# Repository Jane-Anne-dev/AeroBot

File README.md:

# Starbie

Aerobot is a personal desk buddy. It can be any shape, the goal is to be creative. I t has a motion sensor which allows aerobot  to know if tis being moved around.
shake it and its face moves!
## What it is
It sits on your desk as a companion. You can assign different functions with the buttons and you can play with it if you're bored.

It is inspired by the starbie, here is the repository: https://github.com/SharKingStudios/Starbie/blob/main/README.md?plain=1
it is equiped with a guide which i followed.

The board includes an oled display, microcontroller and motion sensor

The firmware is in the main.cpp file

The aerobot has 21 expressions:
 Mood button cycle (starts in AUTO at boot, never returns to it):
//     Tap  1 Happy         Tap  2 Wink          Tap  3 Love
//     Tap  4 Sleepy        Tap  5 Cry           Tap  6 Distressed
//     Tap  7 Glare         Tap  8 Mad           Tap  9 Glasses
//     Tap 10 Sleep         Tap 11 Blink upper   Tap 12 Tired
//     Tap 13 Night         Tap 14 Upper lids    Tap 15 Lower lids
//     Tap 16 Blank         Tap 17 "HELLO"       Tap 18 "BYE"
//     Tap 19 "What?"       Tap 20 Scuba Cat (sways side to side)
//     Tap 21 = back to Happy ... and so on forever

It also signals water me when it senses dry soil
The 3rd button turns the screen off
The 4th button recaliberates the mpu6050

The aerobot is now comple. Please access the BOM.md for a proper breakdown of the necessary components. The journal for help with any struggles, as i may have struggled with the same thing. 
The KiCad folder has all the schematics, and pcb render. As well as gerber  file which has to be zipped if you  want to order the pcb I made form JLC PCB.
The main.cpp is the program to be installed in the ESP32 C3. it is built for an oled with the sh1106 driver. If you have a different OLED, just change the libraries and it should work.

There's also the backup firmware which is just a copy of main.cpp in case the file gets missing.

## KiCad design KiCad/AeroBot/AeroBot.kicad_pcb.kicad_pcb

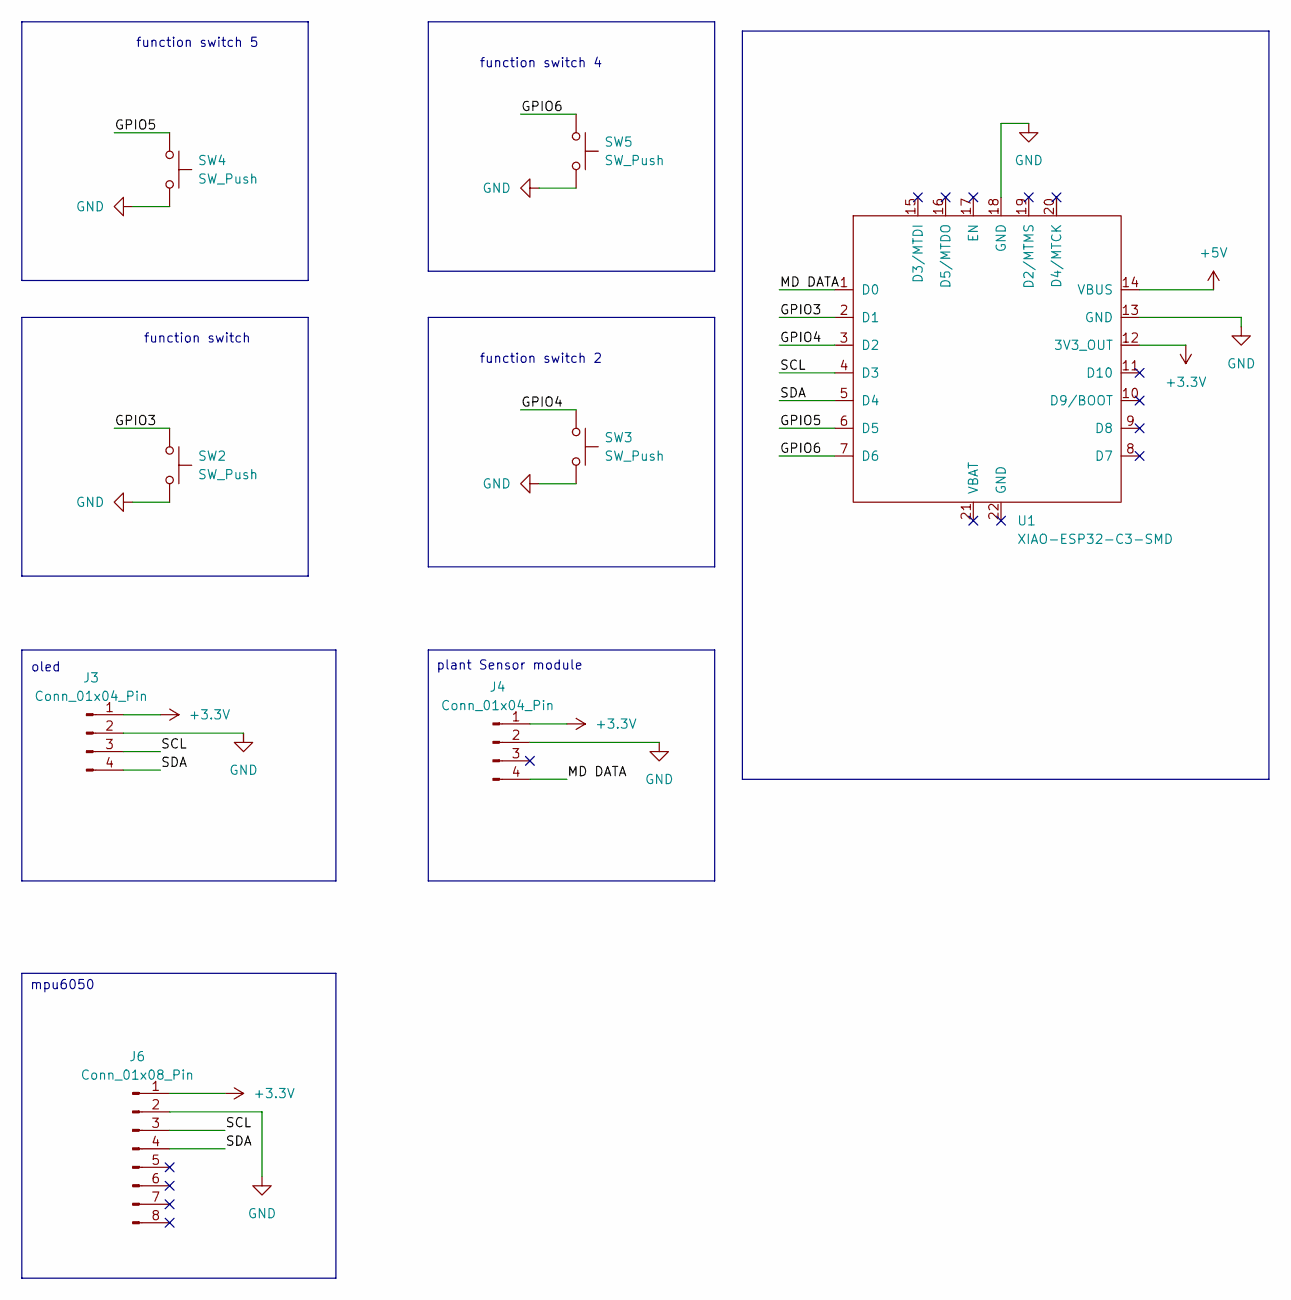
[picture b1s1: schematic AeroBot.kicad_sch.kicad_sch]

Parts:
J3, J4: Conn_01x04_Pin; PinHeader_1x04_P2.54mm_Vertical
J6: Conn_01x08_Pin; PinHeader_1x08_P2.54mm_Vertical
SW2, SW3, SW4, SW5: SW_Push; SW_PUSH_6mm
U1: XIAO-ESP32-C3-SMD

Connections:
+3.3V: J3.1, J4.1, J6.1, U1.12 (3V3_OUT)
+5V: U1.14 (VBUS)
/GPIO3: SW2.1, U1.2 (D1)
/GPIO4: SW3.1, U1.3 (D2)
/GPIO5: SW4.1, U1.6 (D5)
/GPIO6: SW5.1, U1.7 (D6)
/MD DATA: J4.4, U1.1 (D0)
/SCL: J3.3, J6.3, U1.4 (D3)
/SDA: J3.4, J6.4, U1.5 (D4)
GND: J3.2, J4.2, J6.2, SW2.2, SW3.2, SW4.2, SW5.2, U1.13 (GND), U1.18 (GND)

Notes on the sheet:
function switch 5
function switch 4
function switch
plant Sensor module
oled
function switch 2
mpu6050

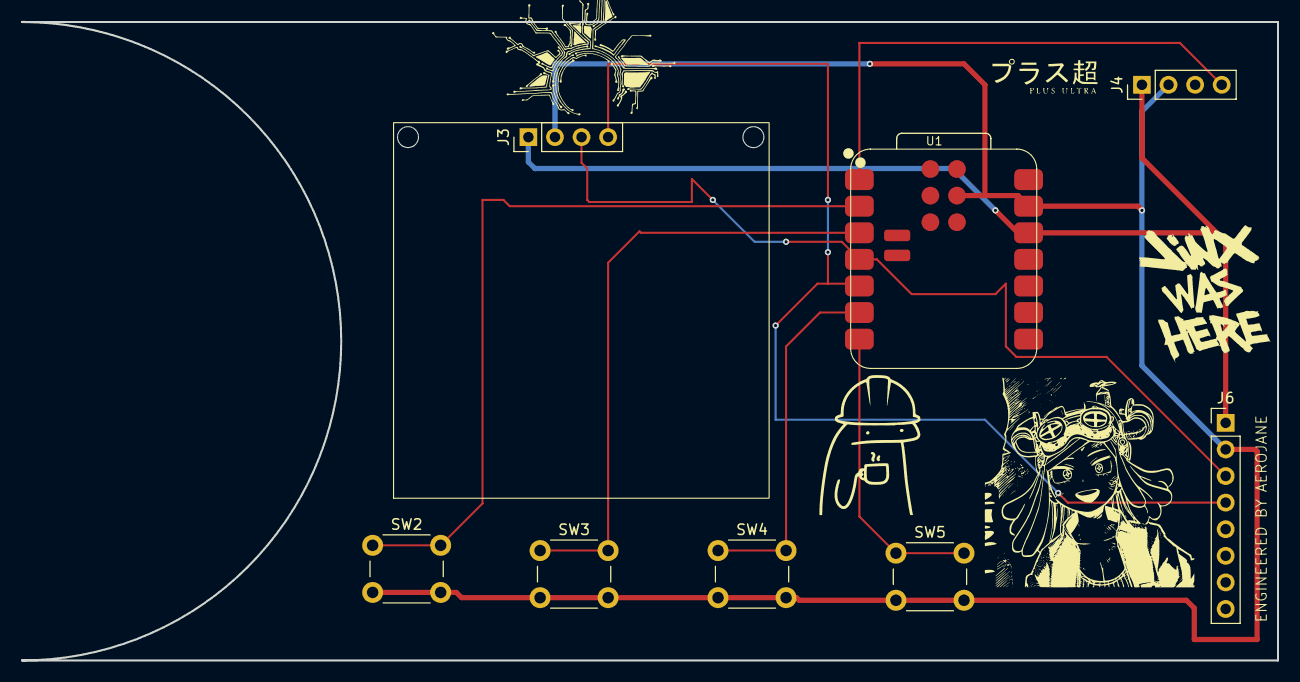
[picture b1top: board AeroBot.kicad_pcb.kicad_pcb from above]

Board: 2 copper layers, 120.0 x 61.0 mm, 8 parts (0 on the bottom side), 9 nets.
